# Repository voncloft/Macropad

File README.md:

Hopefully a simple project to push thru on March 31st 2026

A macropad with Wifi, Bluetooth, IR TX and RX, and battery operated

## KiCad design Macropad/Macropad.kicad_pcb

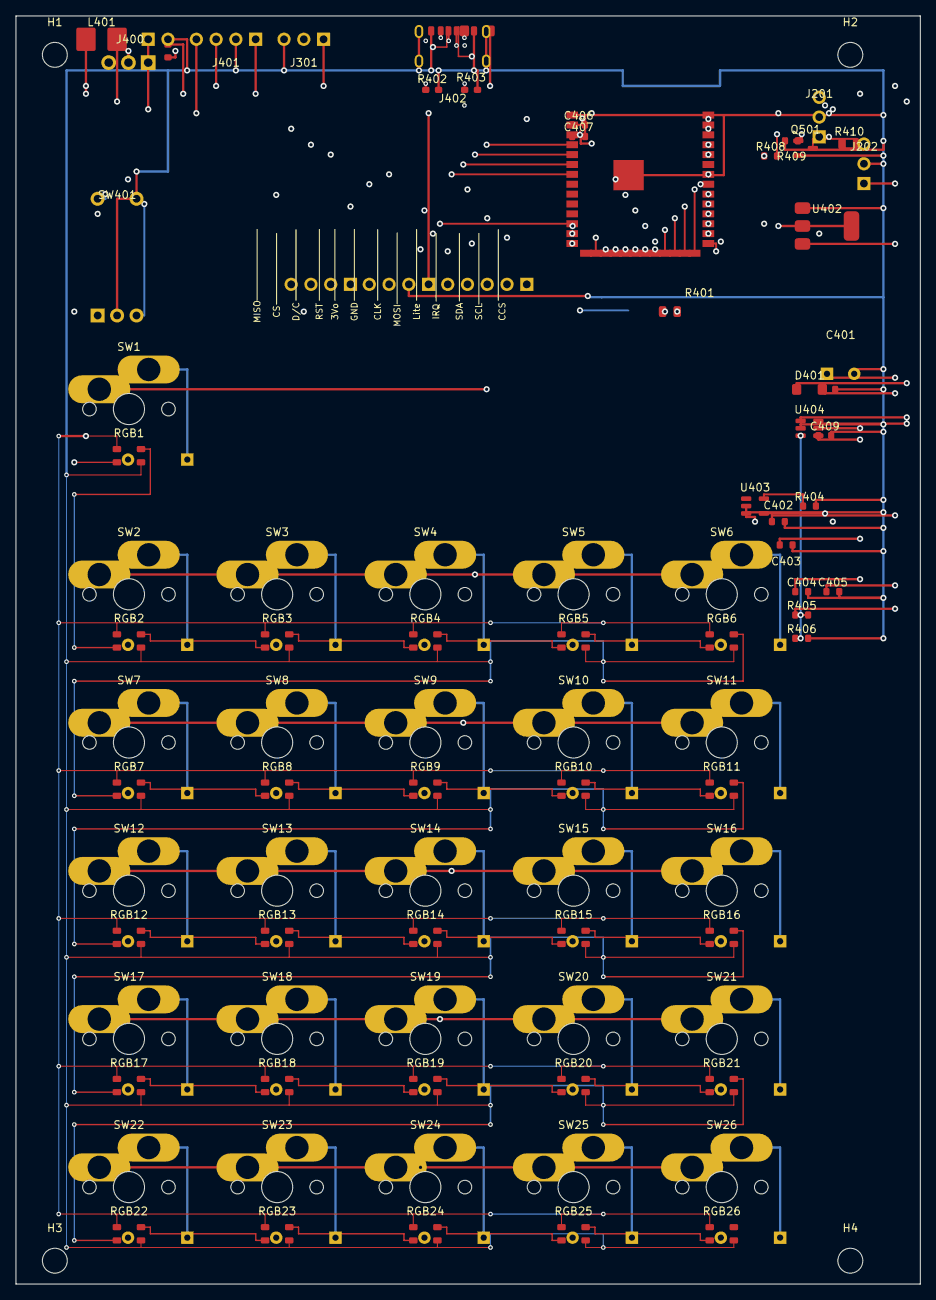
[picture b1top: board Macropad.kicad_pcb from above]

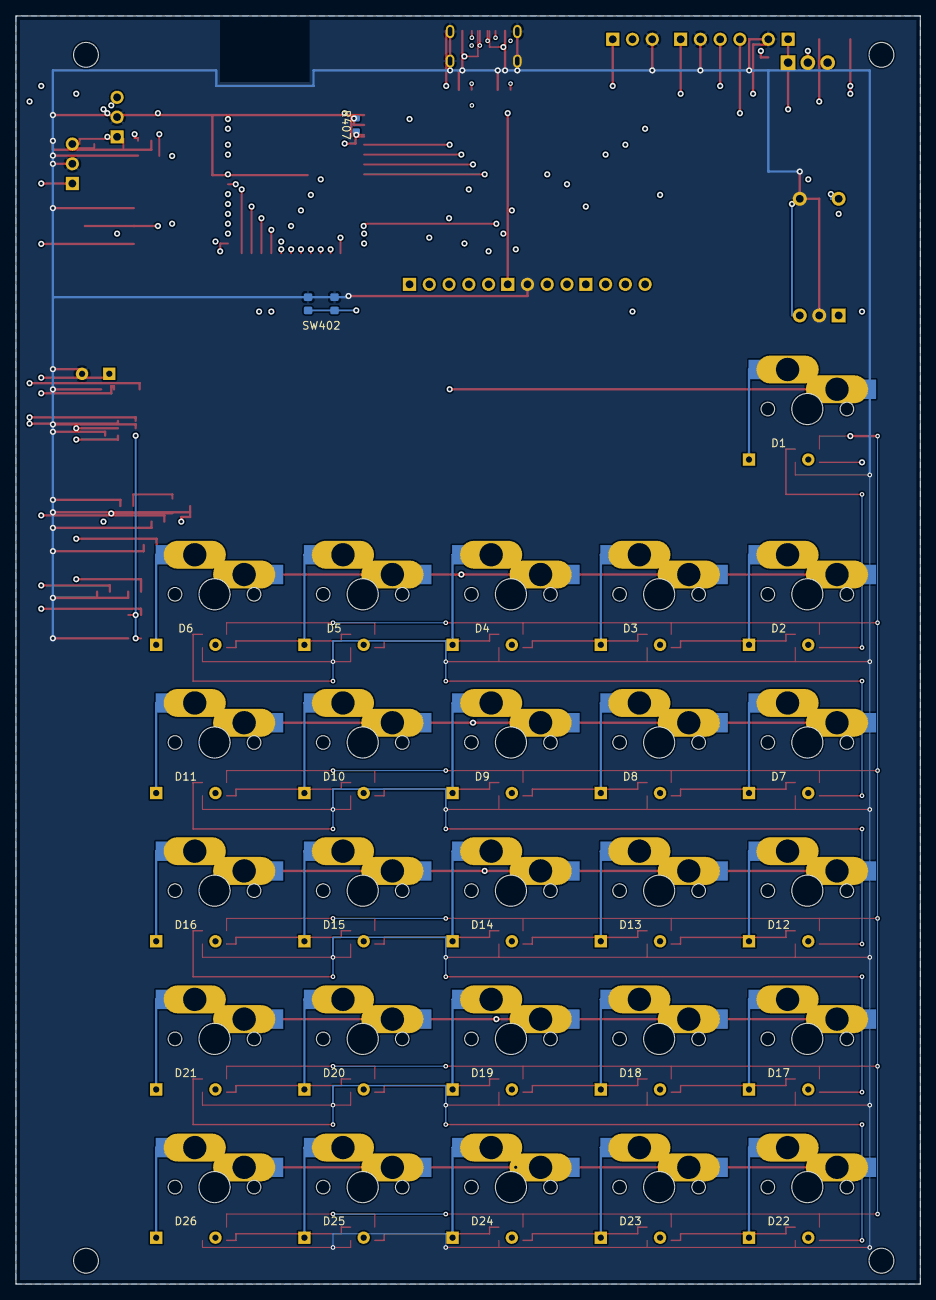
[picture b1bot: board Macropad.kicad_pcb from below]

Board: 4 copper layers, 116.2 x 163.0 mm, 122 parts (28 on the bottom side), 98 nets.

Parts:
C401: 470uF; GEN_CP_Radial_D8_P3.5
C402: 1uF; C_0603_1608Metric_LOCAL
C403: 4.7uF; C_0603_1608Metric_LOCAL
C404, C405, C408, C409: 10uF; C_0603_1608Metric_LOCAL
C406: 100nF; C_0603_1608Metric_LOCAL
C407: 22uF; C_0603_1608Metric_LOCAL
D1, D2, D3, D4, D5, D6, D7, D8, D9, D10, D11, D12, D13, D14, D15, D16, D17, D18, D19, D20, D21, D22, D23, D24, D25, D26: D; D_DO35_Custom
D401: SS14; D_SOD123_LOCAL
D402: SS14_VBUS_TO_5VSYS; D_SOD123_LOCAL
F401: PTC_0.5A; R_0603_1608Metric_LOCAL
H1, H2, H3, H4: MountingHole; GEN_MountingHole_3.2mm_M3
J201: TSOP4838_C124647; GEN_PinHeader_1x3_P2.54
J202: IR_LED_TX_HDR; GEN_PinHeader_1x3_P2.54
J301: LED_CHAIN; GEN_PinHeader_1x3_P2.54
J302: LCD_SPI_PWRDATA; GEN_PinHeader_1x4_P2.54
J303: LCD_SPI_CTRL; GEN_PinHeader_1x4_P2.54
J304: TOUCH_I2C_SD_IRQ; GEN_PinHeader_1x5_P2.54
J400: BATTERY_LIPO; GEN_PinHeader_1x2_P2.54
J401: BAT_CHG_BOOST; GEN_PinHeader_1x4_P2.54
J402: USB_C_CHG_IN; USB_C_Receptacle_GCT_USB4125_6P_LOCAL
L401: 4.7uH; L_Boost_5x5_LOCAL
Q501: AO3400A; SOT-23_LOCAL
R401: 330R; R_0805_2012Metric_LOCAL
R402, R403: 5.1k; R_0603_1608Metric_LOCAL
R404: 3.3k; R_0603_1608Metric_LOCAL
R405: 162k; R_0603_1608Metric_LOCAL
R406: 22k; R_0603_1608Metric_LOCAL
R407: 10k; R_0603_1608Metric_LOCAL
R408: 100R; R_0603_1608Metric_LOCAL
R409: 100k; R_0603_1608Metric_LOCAL
R410: 47R; R_0805_2012Metric_LOCAL
RGB1, RGB2, RGB3, RGB4, RGB5, RGB6, RGB7, RGB8, RGB9, RGB10, RGB11, RGB12, RGB13, RGB14, RGB15, RGB16, RGB17, RGB18, RGB19, RGB20, RGB21, RGB22, RGB23, RGB24, RGB25, RGB26: SK6812MINI; RGB_PLACEHOLDER_3535
SW1, SW2, SW3, SW4, SW5, SW6, SW7, SW8, SW9, SW10, SW11, SW12, SW13, SW14, SW15, SW16, SW17, SW18, SW19, SW20, SW21, SW22, SW23, SW24, SW25, SW26: SW_Push; Kailh_Hotswap_MX_1U_Custom
SW401: RotaryEncoder_Switch; GEN_RotaryEncoder_EC11_Switch
SW402: MSS-102545-14A-V-SMT; SW_Slide_SPDT_BATTERY_KILL_MSS-102545-14A-V-SMT_LOCAL
SW402#2: SW_Push; SW_TACT_3x6_4P_LOCAL
U402: AP7361C-33E; SOT-223-3_TabPin2_LOCAL
U403: MCP73831; SOT-23-5_LOCAL
U404: MT3608; SOT-23-6_LOCAL
U901: ESP32-S3-WROOM-1-N8R8; ESP32-S3-WROOM-1_LOCAL

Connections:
3V3: C406.1, C407.1, J201.1, J302.1, J401.4, R407.2, U402.2, U901.2
5V_SYS: C401.1, C402.1, C405.1, C408.1, D401.2, D402.2, J202.1, J301.1, J401.3, R405.1, RGB1.1, RGB2.1, RGB3.1, RGB4.1, RGB5.1, RGB6.1, RGB7.1, RGB8.1, RGB9.1, RGB10.1, RGB11.1, RGB12.1, RGB13.1, RGB14.1, RGB15.1, RGB16.1, RGB17.1, RGB18.1, RGB19.1, RGB20.1, RGB21.1, RGB22.1, RGB23.1, RGB24.1, RGB25.1, RGB26.1, U402.3
BAT+: C403.1, C404.1, C409.1, F401.2, J401.1, L401.1, U404.4, U404.5
BAT_RAW: J400.1, SW402.1, U403.3
BAT_SW: F401.1, SW402.2
BOOST_FB: R405.2, R406.1, U404.3
BOOST_SW: D401.1, L401.2, U404.1, U404.6
CHG_PROG: R404.1, U403.5
COL0: D1.2, D2.2, D7.2, D12.2, D17.2, D22.2, U901.18
COL1: D3.2, D8.2, D13.2, D18.2, D23.2, U901.19
COL2: D4.2, D9.2, D14.2, D19.2, D24.2, U901.20
COL3: D5.2, D10.2, D15.2, D20.2, D25.2, U901.21
COL4: D6.2, D11.2, D16.2, D21.2, D26.2, U901.22
EN: R407.1, SW402#2.1, U901.3
ENC_A: SW401.A, U901.30
ENC_B: SW401.B, U901.31
ENC_SW: SW401.S1, U901.32
GND: C401.2, C402.2, C403.2, C404.2, C405.2, C406.2, C407.2, C408.2, C409.2, J201.2, J202.2, J301.3, J302.2, J400.2, J401.2, J402.A12, J402.B12, J402.S1, Q501.2, R402.2, R403.2, R404.2, R406.2, R409.2, RGB1.3, RGB2.3, RGB3.3, RGB4.3, RGB5.3, RGB6.3, RGB7.3, RGB8.3, RGB9.3, RGB10.3, RGB11.3, RGB12.3, RGB13.3, RGB14.3, RGB15.3, RGB16.3, RGB17.3, RGB18.3, RGB19.3, RGB20.3, RGB21.3, RGB22.3, RGB23.3, RGB24.3, RGB25.3, RGB26.3, SW401.C, SW401.S2, SW402#2.2, U402.1, U403.2, U404.2, U901.1, U901.40, U901.41
IR_LED_K: J202.3, R410.1
IR_LED_SW: Q501.3, R410.2
IR_RX: J201.3, U901.28
IR_TX: R408.1, U901.29
IR_TX_GATE: Q501.1, R408.2, R409.1
K1: D1.1, SW1.2
K2: D2.1, SW2.2
K3: D3.1, SW3.2
K4: D4.1, SW4.2
K5: D5.1, SW5.2
K6: D6.1, SW6.2
K7: D7.1, SW7.2
K8: D8.1, SW8.2
K9: D9.1, SW9.2
K10: D10.1, SW10.2
K11: D11.1, SW11.2
K12: D12.1, SW12.2
K13: D13.1, SW13.2
K14: D14.1, SW14.2
K15: D15.1, SW15.2
K16: D16.1, SW16.2
K17: D17.1, SW17.2
K18: D18.1, SW18.2
K19: D19.1, SW19.2
K20: D20.1, SW20.2
K21: D21.1, SW21.2
K22: D22.1, SW22.2
K23: D23.1, SW23.2
K24: D24.1, SW24.2
K25: D25.1, SW25.2
K26: D26.1, SW26.2
LCD_BL: J304.1, U901.39
LCD_CS: J303.2, U901.36
LCD_DC: J303.3, U901.37
LCD_MOSI: J302.4, U901.33
LCD_RST: J303.4, U901.38
LCD_SCLK: J302.3, U901.34
LED_DIN: J301.2, R401.2, RGB1.4
RGB1_DOUT: RGB1.2, RGB2.4
RGB2_DOUT: RGB2.2, RGB3.4
RGB3_DOUT: RGB3.2, RGB4.4
RGB4_DOUT: RGB4.2, RGB5.4
RGB5_DOUT: RGB5.2, RGB6.4
RGB6_DOUT: RGB6.2, RGB7.4
RGB7_DOUT: RGB7.2, RGB8.4
RGB8_DOUT: RGB8.2, RGB9.4
RGB9_DOUT: RGB9.2, RGB10.4
RGB10_DOUT: RGB10.2, RGB11.4
RGB11_DOUT: RGB11.2, RGB12.4
RGB12_DOUT: RGB12.2, RGB13.4
RGB13_DOUT: RGB13.2, RGB14.4
RGB14_DOUT: RGB14.2, RGB15.4
RGB15_DOUT: RGB15.2, RGB16.4
RGB16_DOUT: RGB16.2, RGB17.4
RGB17_DOUT: RGB17.2, RGB18.4
RGB18_DOUT: RGB18.2, RGB19.4
RGB19_DOUT: RGB19.2, RGB20.4
RGB20_DOUT: RGB20.2, RGB21.4
RGB21_DOUT: RGB21.2, RGB22.4
RGB22_DOUT: RGB22.2, RGB23.4
RGB23_DOUT: RGB23.2, RGB24.4
RGB24_DOUT: RGB24.2, RGB25.4
RGB25_DOUT: RGB25.2, RGB26.4
RGB_DATA: R401.1, U901.23
ROW0: SW1.1, U901.4
ROW1: SW2.1, SW3.1, SW4.1, SW5.1, SW6.1, U901.5
ROW2: SW7.1, SW8.1, SW9.1, SW10.1, SW11.1, U901.6
ROW3: SW12.1, SW13.1, SW14.1, SW15.1, SW16.1, U901.7
ROW4: SW17.1, SW18.1, SW19.1, SW20.1, SW21.1, U901.12
ROW5: SW22.1, SW23.1, SW24.1, SW25.1, SW26.1, U901.17
SD_CS: J304.5, U901.27
SPI_MISO: J303.1, U901.25
TOUCH_INT: J304.2, U901.16
TOUCH_SCL: J304.4, U901.26
TOUCH_SDA: J304.3, U901.24
USB_CC1: J402.A5, R402.1
USB_CC2: J402.B5, R403.1
USB_DN: J402.A7, J402.B7, U901.13
USB_DP: J402.A6, J402.B6, U901.14
VBUS: D402.1, J402.A9, J402.B9, U403.4

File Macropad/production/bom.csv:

Designator,Footprint,Quantity,Value,LCSC Part #
C401,GEN_CP_Radial_D8_P3.5,1,470uF,
C402,0603,1,1uF,
C403,0603,1,4.7uF,
"C404, C405, C408, C409",0603,4,10uF,
C406,0603,1,100nF,
C407,0603,1,22uF,
"D1, D10, D11, D12, D13, D14, D15, D16, D17, D18, D19, D2, D20, D21, D22, D23, D24, D25, D26, D3, D4, D5, D6, D7, D8, D9",D_DO35_Custom,26,D,
D401,D_SOD123_LOCAL,1,SS14,
D402,D_SOD123_LOCAL,1,SS14_VBUS_TO_5VSYS,
F401,0603,1,PTC_0.5A,
J201,GEN_PinHeader_1x3_P2.54,1,TSOP4838_C124647,
J202,GEN_PinHeader_1x3_P2.54,1,IR_LED_TX_HDR,
J301,GEN_PinHeader_1x3_P2.54,1,LED_CHAIN,
J302,GEN_PinHeader_1x4_P2.54,1,LCD_SPI_PWRDATA,
J303,GEN_PinHeader_1x4_P2.54,1,LCD_SPI_CTRL,
J304,GEN_PinHeader_1x5_P2.54,1,TOUCH_I2C_SD_IRQ,
J400,GEN_PinHeader_1x2_P2.54,1,BATTERY_LIPO,
J401,GEN_PinHeader_1x4_P2.54,1,BAT_CHG_BOOST,
J402,USB_C_Receptacle_GCT_USB4125_6P_LOCAL,1,USB_C_CHG_IN,
JP403,GEN_PinHeader_1x2_P2.54,1,SHIP_JUMPER,
L401,L_Boost_5x5_LOCAL,1,4.7uH,
Q501,SOT-23_LOCAL,1,AO3400A,
R401,0805,1,330R,
"R402, R403",0603,2,5.1k,
R404,0603,1,3.3k,
R405,0603,1,162k,
R406,0603,1,22k,
R407,0603,1,10k,
R408,0603,1,100R,
R409,0603,1,100k,
R410,0805,1,47R,
"RGB1, RGB10, RGB11, RGB12, RGB13, RGB14, RGB15, RGB16, RGB17, RGB18, RGB19, RGB2, RGB20, RGB21, RGB22, RGB23, RGB24, RGB25, RGB26, RGB3, RGB4, RGB5, RGB6, RGB7, RGB8, RGB9",RGB_PLACEHOLDER_3535,26,SK6812MINI,
"SW1, SW10, SW11, SW12, SW13, SW14, SW15, SW16, SW17, SW18, SW19, SW2, SW20, SW21, SW22, SW23, SW24, SW25, SW26, SW3, SW4, SW5, SW6, SW7, SW8, SW9",Kailh_Hotswap_MX_1U_Custom,26,SW_Push,
SW401,GEN_RotaryEncoder_EC11_Switch,1,RotaryEncoder_Switch,
SW402,SW_TACT_3x6_4P_LOCAL,1,SW_Push,
U402,SOT-223-3_TabPin2_LOCAL,1,AP7361C-33E,
U403,SOT-23-5_LOCAL,1,MCP73831,
U404,SOT-23-6_LOCAL,1,MT3608,
U901,ESP32-S3-WROOM-1_LOCAL,1,ESP32-S3-WROOM-1-N8R8,

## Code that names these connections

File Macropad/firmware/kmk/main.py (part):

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
# Placeholder extension setup (replace with your board pin mapping).
rgb = RGB(
    pixel_pin=_must_pin(RGB_DATA_PAD, "RGB_DATA"),
    num_pixels=26,
    val_default=28,          # conservative default brightness
)
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encoder_handler = EncoderHandler()
encoder_handler.pins = (
    (
        _must_pin(ENC_A_PAD, "ENC_A"),
        _must_pin(ENC_B_PAD, "ENC_B"),
        _must_pin(ENC_SW_PAD, "ENC_SW"),
    ),
)
keyboard.modules.append(encoder_handler)

keyboard.row_pins = (
    _must_pin(ROW0_PAD, "ROW0"),
    _must_pin(ROW1_PAD, "ROW1"),
    _must_pin(ROW2_PAD, "ROW2"),
    _must_pin(ROW3_PAD, "ROW3"),
    _must_pin(ROW4_PAD, "ROW4"),
    _must_pin(ROW5_PAD, "ROW5"),
)
keyboard.col_pins = (
    _must_pin(COL0_PAD, "COL0"),
    _must_pin(COL1_PAD, "COL1"),
    _must_pin(COL2_PAD, "COL2"),
    _must_pin(COL3_PAD, "COL3"),
    _must_pin(COL4_PAD, "COL4"),
)
keyboard.diode_orientation = DiodeOrientation.COL2ROW

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
# LCD panel + touch pin mapping placeholders. Update to your board mapping.
# Resolver supports both explicit board pin names and RP2040-style pad numbers.
LCD_DC_PIN_NAME = "LCD_DC"
LCD_CS_PIN_NAME = "LCD_CS"
LCD_RST_PIN_NAME = "LCD_RST"
LCD_BL_PIN_NAME = "LCD_BL"
LCD_SPI_SCK_PIN_NAME = "LCD_SCL"
LCD_SPI_MOSI_PIN_NAME = "LCD_SDA"
LCD_SPI_MISO_PIN_NAME = "LCD_MISO"
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
            pin = _optional_pin(IR_TX_PAD)
            if pin is None:
                _log("IR TX init skipped: unresolved IR_TX pin")
                return False
            pwm = pwmio.PWMOut(
                pin,
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    except Exception:
        return False
    try:
        sck = _must_pin(LCD_SPI_SCLK_PAD, "LCD_SCLK")
        mosi = _must_pin(LCD_SPI_MOSI_PAD, "LCD_MOSI")
        miso = _must_pin(SPI_MISO_PAD, "SPI_MISO")
        cs = digitalio.DigitalInOut(_must_pin(SD_CS_PAD, "SD_CS"))
        spi = busio.SPI(sck, MOSI=mosi, MISO=miso)
        sd = sdcardio.SDCard(spi, cs)
        storage.mount(storage.VfsFat(sd), SD_MOUNT_POINT)
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
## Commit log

2026-02-28 FIRST UPLOAD
2026-03-01 Project Updates
2026-03-01 Fixes
2026-03-01 finished
2026-03-02 DONE DONE DONE
2026-03-02 DONE NOW
2026-03-02 IR INCREASE
2026-03-03 pcb: fix battery/usb power path and charging/boost setpoints
2026-03-03 Finalize macropad firmware + schematic/pcb validation updates
2026-03-03 DONE
2026-03-03 Sync firmware pad map to current PCB USB/touch routing
2026-03-03 Board and firmware updates
2026-03-03 updating firmware
2026-03-03 Firmware revision
